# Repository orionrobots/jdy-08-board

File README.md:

# jdy-08-board
A JDY 08 Breakout Board Design

This has been put together, but the module has not been shown yet to work in this configuration, and additional supporting circuitry may be needed to make the module behave.

This repository includes the recently used Gerber files needed to have the board manufactured.

[More resources on the JDY-08 module](https://github.com/kichMan/JDY-08)

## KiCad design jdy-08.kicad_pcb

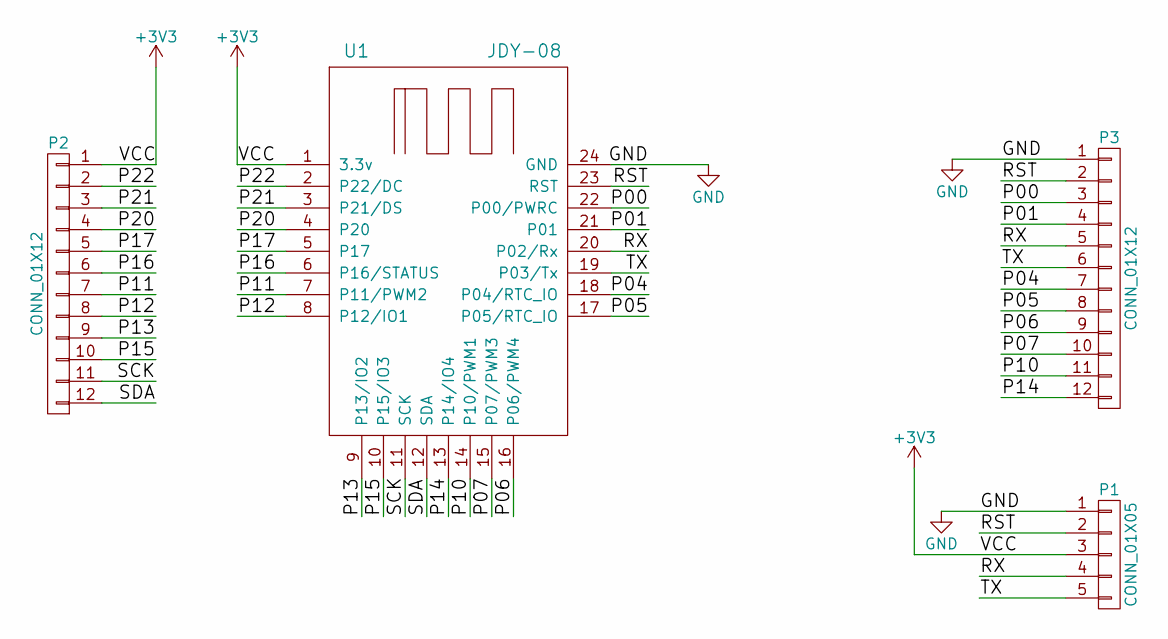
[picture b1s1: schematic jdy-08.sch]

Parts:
P1: CONN_01X05; Socket_Strip_Straight_1x05
P2, P3: CONN_01X12; Socket_Strip_Straight_1x12
U1: JDY-08

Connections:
+3V3: P1.3, P2.1, U1.1 (3.3v)
/P00: P3.3, U1.22 (P00/PWRC)
/P01: P3.4, U1.21 (P01)
/P04: P3.7, U1.18 (P04/RTC_IO)
/P05: P3.8, U1.17 (P05/RTC_IO)
/P06: P3.9, U1.16 (P06/PWM4)
/P07: P3.10, U1.15 (P07/PWM3)
/P10: P3.11, U1.14 (P10/PWM1)
/P11: P2.7, U1.7 (P11/PWM2)
/P12: P2.8, U1.8 (P12/IO1)
/P13: P2.9, U1.9 (P13/IO2)
/P14: P3.12, U1.13 (P14/IO4)
/P15: P2.10, U1.10 (P15/IO3)
/P16: P2.6, U1.6 (P16/STATUS)
/P17: P2.5, U1.5 (P17)
/P20: P2.4, U1.4 (P20)
/P21: P2.3, U1.3 (P21/DS)
/P22: P2.2, U1.2 (P22/DC)
/RST: P1.2, P3.2, U1.23 (RST)
/RX: P1.4, P3.5, U1.20 (P02/Rx)
/SCK: P2.11, U1.11 (SCK)
/SDA: P2.12, U1.12 (SDA)
/TX: P1.5, P3.6, U1.19 (P03/Tx)
GND: P1.1, P3.1, U1.24 (GND)

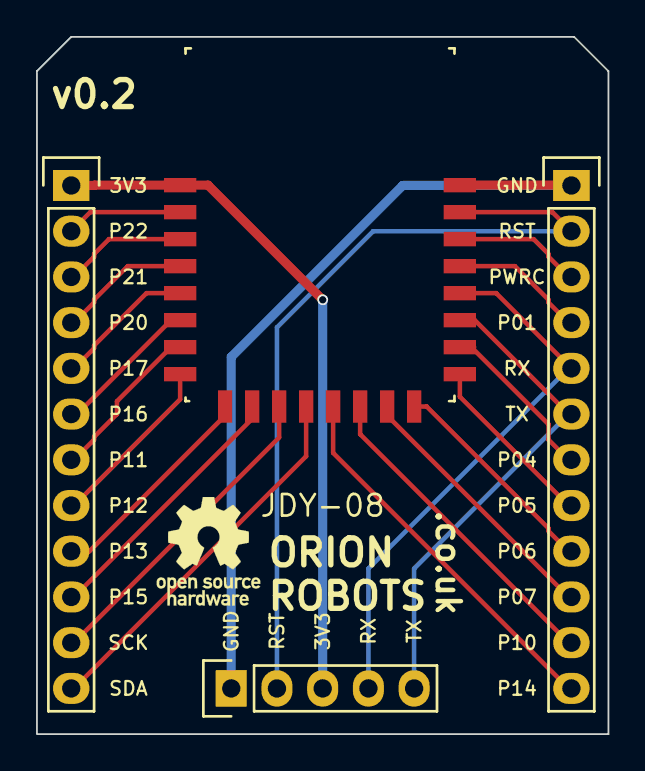
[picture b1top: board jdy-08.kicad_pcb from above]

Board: 2 copper layers, 31.8 x 38.7 mm, 4 parts (0 on the bottom side), 24 nets.

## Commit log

2017-01-13 Initial commit - get this in source control
2017-01-13 Missed file and gitignore.
2017-03-28 Add the current pcb and gerber files
2017-03-28 Filled out readme
2017-03-28 Update video link
2017-06-17 Add link to further resources
